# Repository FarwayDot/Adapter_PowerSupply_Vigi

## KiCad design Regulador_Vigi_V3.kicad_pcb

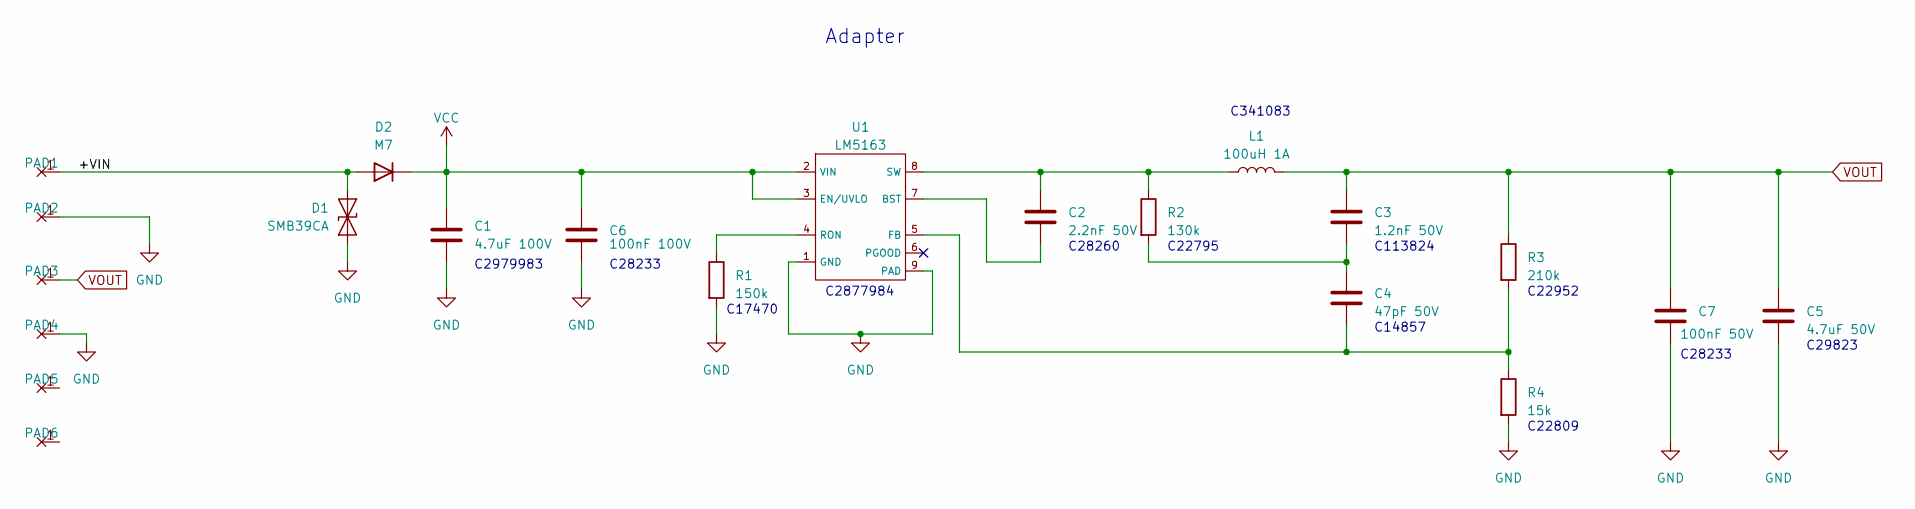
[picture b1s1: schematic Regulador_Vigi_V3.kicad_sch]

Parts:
C1: 4.7uF 100V; C_1210_3225Metric_Mod
C2: 2.2nF 50V; C_0805_2012Metric
C3: 1.2nF 50V; C_0805_2012Metric
C4: 47pF 50V; C_0805_2012Metric
C5: 4.7uF 50V; C_1206_3216Metric
C6: 100nF 100V; C_0805_2012Metric
C7: 100nF 50V; C_0805_2012Metric
D1: SMB39CA; D_SMB
D2: M7; D_SMA
L1: 100uH 1A; L_8x8mm
PAD1, PAD2, PAD3, PAD4, PAD5, PAD6: PAD_2.54_1.0
R1: 150k; R_0805_2012Metric
R2: 130k; R_0603_1608Metric
R3: 210k; R_0603_1608Metric
R4: 15k; R_0603_1608Metric
U1: LM5163; DDA0008E_M

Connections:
/+VIN: D1.1 (A1), D2.2 (A), PAD1.1
GND: C1.2, C5.2, C6.2, C7.2, D1.2 (A2), PAD2.1, PAD4.1, R1.2, R4.2, U1.1 (GND), U1.9 (PAD)
unnamed: C3.2, C4.1, R2.2
unnamed: C2.2, U1.7 (BST)
unnamed: C4.2, R3.2, R4.1, U1.5 (FB)
unnamed: R1.1, U1.4 (RON)
unnamed: C2.1, L1.1, R2.1, U1.8 (SW)
VCC: C1.1, C6.1, D2.1 (K), U1.2 (VIN), U1.3 (EN/UVLO)
VOUT: C3.1, C5.1, C7.1, L1.2, PAD3.1, R3.1

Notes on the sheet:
C14857
C2979983
C22795
C22809
C29823
C28233
C22952
C17470
C341083
Adapter
C2877984
C113824
C28260

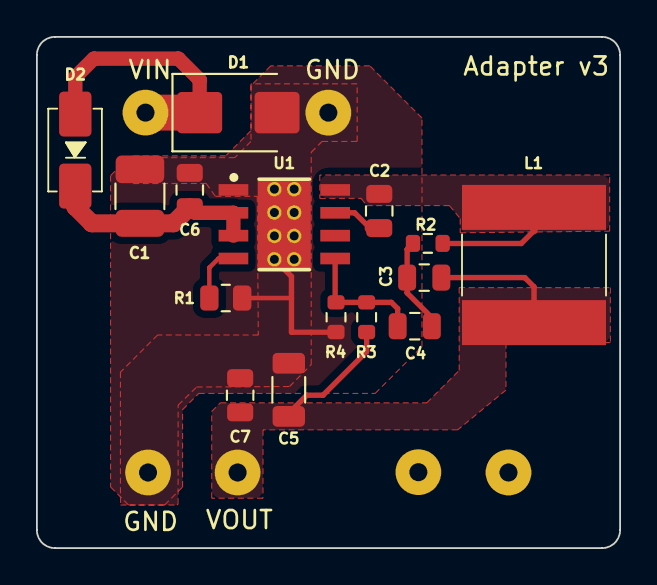
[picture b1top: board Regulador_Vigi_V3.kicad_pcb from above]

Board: 2 copper layers, 32.4 x 28.4 mm, 21 parts (0 on the bottom side), 9 nets.

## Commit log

2023-12-15 Primer commit: Regulador Vigi v3. LM5163 / 24V / 18V 0.5A
2023-12-15 Se terminó el esquemático, Se añadió un capacitor adicional y se cambió el código del inductor
2023-12-15 SCH: Se cambiaron las resistencias del feedback, se limpiaron los comentarios. PCB: Se terminó de rutear. GITIGNORE: se agregó una línea
2024-02-22 SCH:Se cambió comentarios de dos capacitores iniciales para soportar mayor voltaje. PCB:Se actualiza la PCB. JLCPCB:Se cambia el código del part de los capacitores
